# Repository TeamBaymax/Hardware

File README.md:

# Hardware
Hardware Folder

New Folder for Hardware research

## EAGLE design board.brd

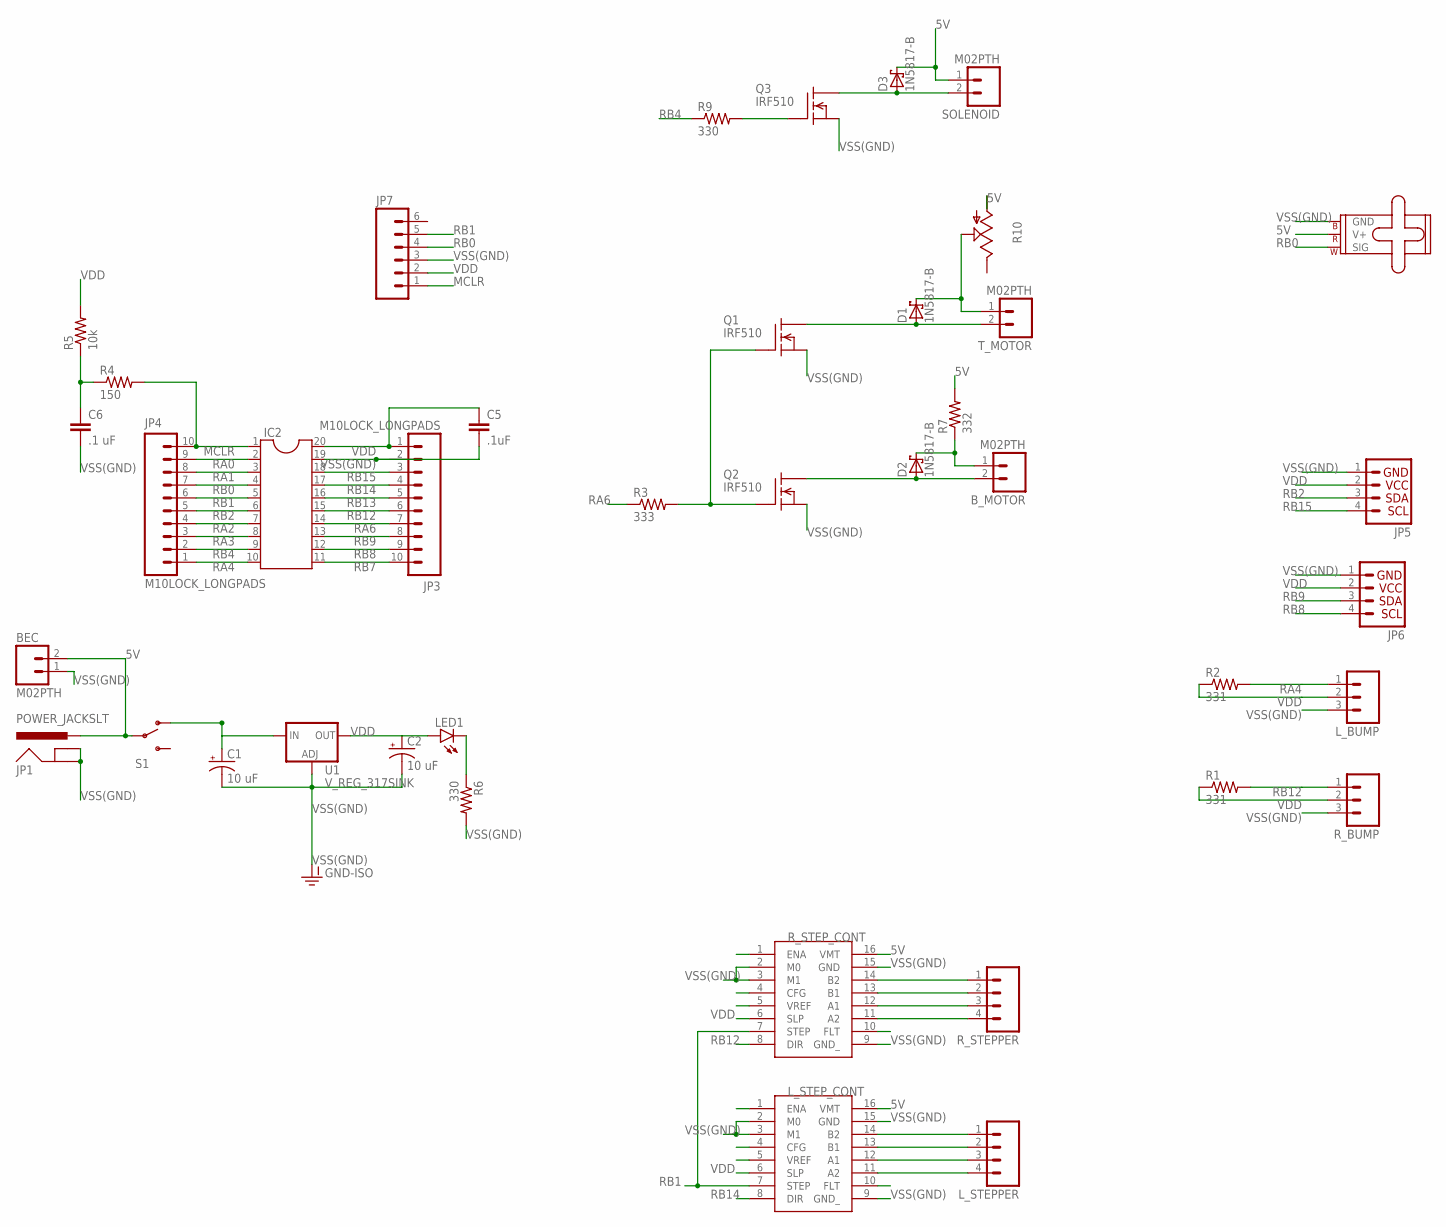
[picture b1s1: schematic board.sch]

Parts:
BEC: M02PTH; 1X02
B_MOTOR: M02PTH; 1X02
C1, C2: 10 uF; CPOL-RADIAL-100UF-25V
C5: .1uF; CAP-PTH-SMALL-KIT
C6: .1 uF; CAP-PTH-SMALL-KIT
D1, D2, D3: 1N5817-B; DO41-7.6
IC2: DIL20S; SOCKET-20
JP1: POWER_JACKSLT; POWER_JACK_SLOT
JP3, JP4: M10LOCK_LONGPADS; 1X10_LOCK_LONGPADS
JP5, JP6: I2C_STANDARD; 1X04
JP7: M06SILK_FEMALE_PTH; 1X06
LED1: LED-3MM-NO_SILK; LED3MM-NS
L_BUMP: M03PTH; 1X03
L_STEPPER: M04PTH; 1X04
L_STEP_CONT: POLOLU
Q1, Q2, Q3: IRF510; TO220
R1, R2: 331; AXIAL-0.4
R3: 333; AXIAL-0.4
R4: 150; AXIAL-0.4
R5: 10k; AXIAL-0.4
R6, R9: 330; AXIAL-0.4
R7: 332; AXIAL-0.4
R10: TRIM_US-B25V; B25V
R_BUMP: M03PTH; 1X03
R_STEPPER: M04PTH; 1X04
R_STEP_CONT: POLOLU
S1: SWITCH-SPDTPTH; SWITCH-SPDT
SOLENOID: M02PTH; 1X02
TURRET: SMALL_SERVO; 1X03
T_MOTOR: M02PTH; 1X02
U1: V_REG_317SINK; TO220-ADJ

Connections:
5V: BEC.2, D3.C, JP1.PWR, L_STEP_CONT.16 (VMT), R7.P$2 (2), R10.A, R_STEP_CONT.16 (VMT), S1.2, SOLENOID.1, TURRET.2 (V+)
MCLR: IC2.1, JP4.10, JP7.1, R4.P$2 (2)
unnamed: C6.1, R4.P$1 (1), R5.P$1 (1)
unnamed: L_STEPPER.1, L_STEP_CONT.14 (B2)
unnamed: R_STEPPER.1, R_STEP_CONT.14 (B2)
unnamed: D1.C, R10.S, T_MOTOR.1
unnamed: D1.A, Q1.2 (D), T_MOTOR.2
unnamed: D3.A, Q3.2 (D), SOLENOID.2
unnamed: Q1.1 (G), Q2.1 (G), R3.P$2 (2)
unnamed: B_MOTOR.1, D2.C, R7.P$1 (1)
unnamed: B_MOTOR.2, D2.A, Q2.2 (D)
unnamed: Q3.1 (G), R9.P$2 (2)
unnamed: C1.1 (+), S1.1 (O), U1.IN
unnamed: LED1.K (C), R6.P$1 (1)
unnamed: R_STEPPER.2, R_STEP_CONT.13 (B1)
unnamed: R_STEPPER.3, R_STEP_CONT.12 (A1)
unnamed: R_STEPPER.4, R_STEP_CONT.11 (A2)
unnamed: L_STEPPER.2, L_STEP_CONT.13 (B1)
unnamed: L_STEPPER.3, L_STEP_CONT.12 (A1)
unnamed: L_STEPPER.4, L_STEP_CONT.11 (A2)
RA0: IC2.2, JP4.9
RA1: IC2.3, JP4.8
RA2: IC2.7, JP4.4
RA3: IC2.8, JP4.3
RA4: IC2.10, JP4.1, L_BUMP.1, R2.P$2 (2)
RA6: IC2.14, JP3.7, R3.P$1 (1)
RB0: IC2.4, JP4.7, JP7.4, TURRET.1 (SIG)
RB1: IC2.5, JP4.6, JP7.5, L_STEP_CONT.7 (STEP), R_STEP_CONT.7 (STEP)
RB2: IC2.6, JP4.5, JP5.3
RB4: IC2.9, JP4.2, R9.P$1 (1)
RB7: IC2.11, JP3.10
RB8: IC2.12, JP3.9, JP6.4
RB9: IC2.13, JP3.8, JP6.3
RB12: IC2.15, JP3.6, R1.P$2 (2), R_BUMP.1, R_STEP_CONT.8 (DIR)
RB13: IC2.16, JP3.5
RB14: IC2.17, JP3.4, L_STEP_CONT.8 (DIR)
RB15: IC2.18, JP3.3, JP5.4
VDD: C2.1 (+), C5.1, IC2.20, JP3.1, JP5.2, JP6.2, JP7.2, LED1.A, L_BUMP.2, L_STEP_CONT.6 (SLP), R1.P$1 (1), R2.P$1 (1), R5.P$2 (2), R_BUMP.2, R_STEP_CONT.6 (SLP), U1.OUT
VSS(GND): BEC.1, C1.2 (-), C2.2 (-), C5.2, C6.2, IC2.19, JP1.GND@1 (GNDBREAK), JP1.GND@2 (GND), JP3.2, JP5.1, JP6.1, JP7.3, L_BUMP.3, L_STEP_CONT.2 (M0), L_STEP_CONT.3 (M1), L_STEP_CONT.9 (GND_), L_STEP_CONT.15 (GND), Q1.3 (S), Q2.3 (S), Q3.3 (S), R6.P$2 (2), R_BUMP.3, R_STEP_CONT.2 (M0), R_STEP_CONT.3 (M1), R_STEP_CONT.9 (GND_), R_STEP_CONT.15 (GND), TURRET.3 (GND), U1.ADJ

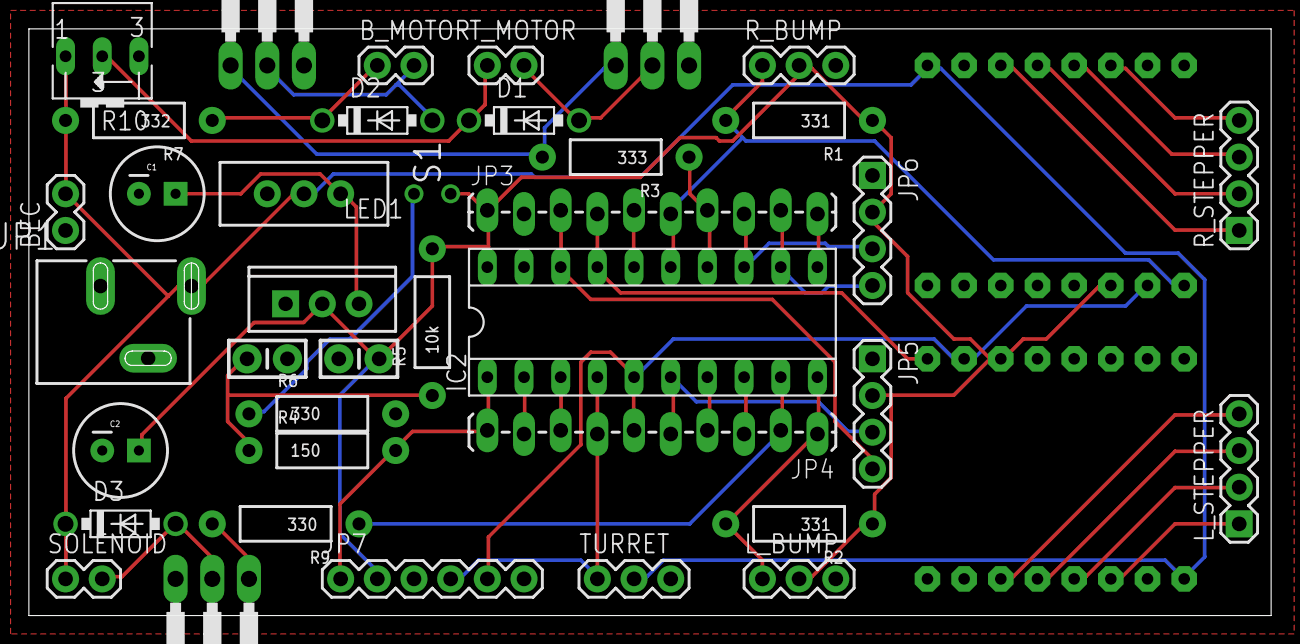
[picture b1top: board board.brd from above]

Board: 2 copper layers, 86.0 x 40.6 mm, 40 parts (0 on the bottom side), 39 nets.

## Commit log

2015-02-24 Create README
    Here is a Readme
2015-02-28 Initial commit of main board schematic and pololu stepper library file
2015-03-03 board designed, minor changes to schematic

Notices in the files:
parts and their libraries:
SparkFun-Connectors: Licensing: Creative Commons ShareAlike 4.0 International - https://creativecommons.org/licenses/by-sa/4.0
